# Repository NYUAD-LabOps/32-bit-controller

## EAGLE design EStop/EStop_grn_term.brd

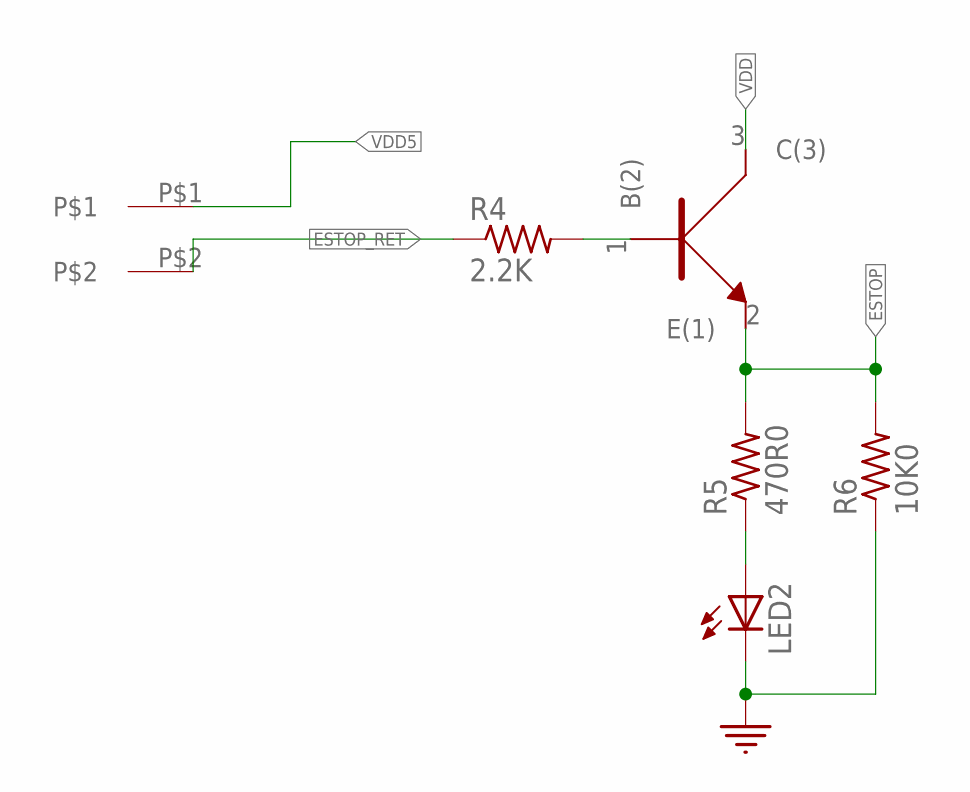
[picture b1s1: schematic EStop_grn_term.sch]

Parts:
J1: 2-pos; 2_3.81MM_PITCH
LED2: Green; 0805
R4: 2.2K; 0402
R5: 470R0; 0402
R6: 10K0; 0402
U2: NPN; SOT323

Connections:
ESTOP: R5.P$2 (2), R6.P$2 (2), U2.2 (E(1))
ESTOP_RET: J1.P$2, R4.P$1 (1)
GND: LED2.2 (C), R6.P$1 (1)
unnamed: R4.P$2 (2), U2.1 (B(2))
unnamed: LED2.1 (A), R5.P$1 (1)
VDD: U2.3 (C(3))
VDD5: J1.P$1

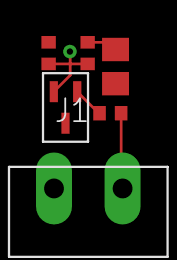
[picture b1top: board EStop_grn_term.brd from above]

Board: 2 copper layers, 6 parts (0 on the bottom side), 5 nets.

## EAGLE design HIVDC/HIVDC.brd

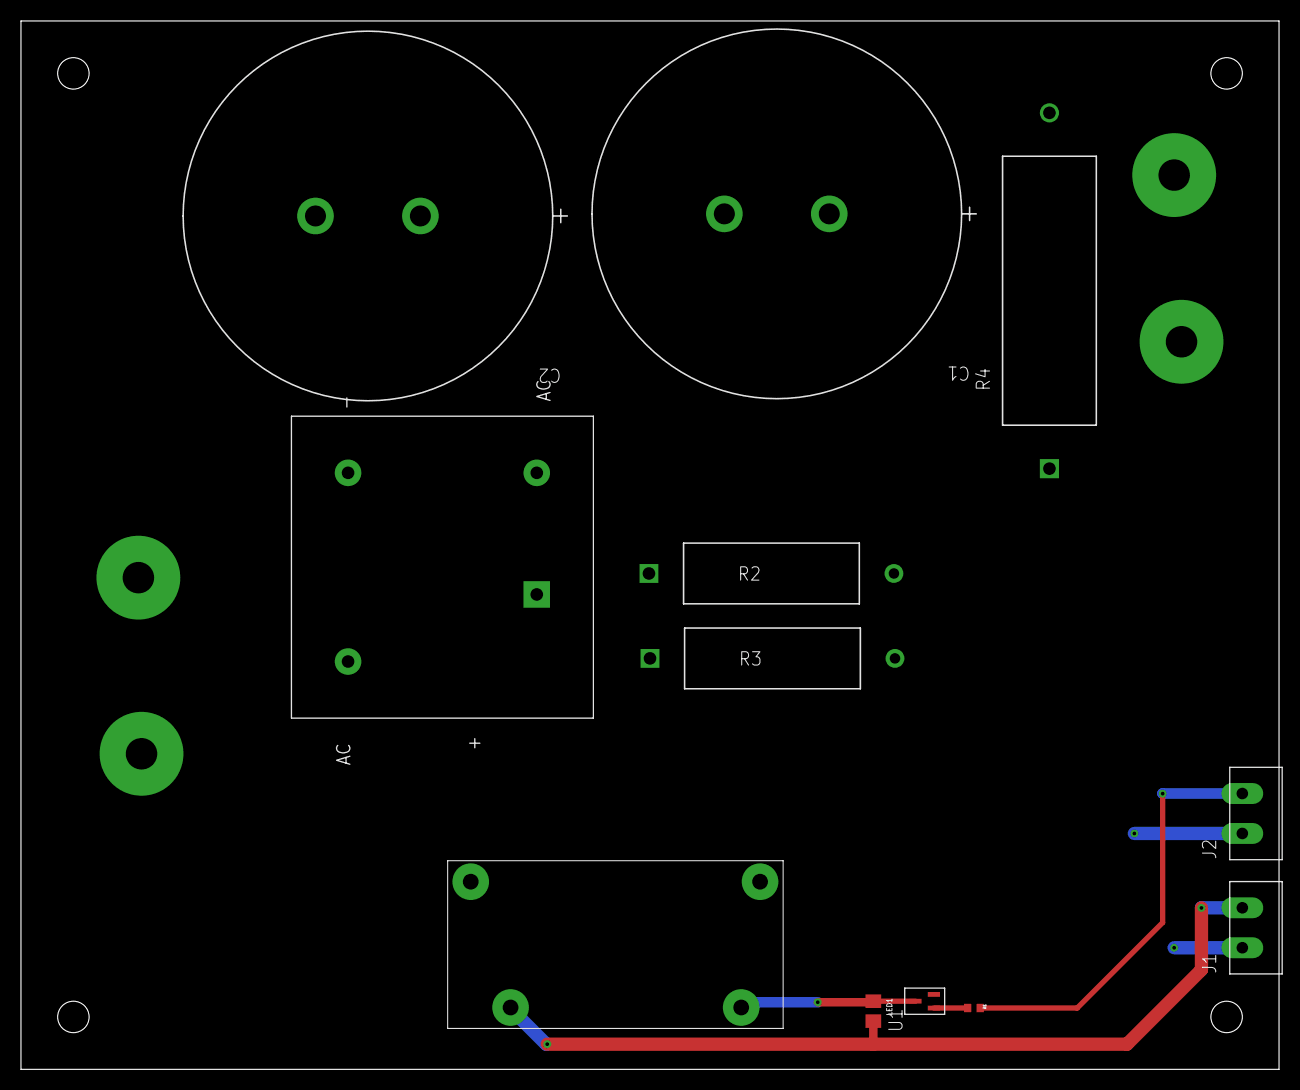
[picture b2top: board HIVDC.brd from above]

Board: 2 copper layers, 120.0 x 100.0 mm, 16 parts (0 on the bottom side), 11 nets.

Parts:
AC_L1: AC_240V_L1_15A
AC_N: AC_240V_L1_15A
C1, C2: SLP152M250H9P3; CAP_SLP152M250H9P3_CND
J1, J2: 2-pos; 2_3.81MM_PITCH
L1, L2: AC_240V_L1_15A
LED1: Green; 0805
R1: 0402
R2, R3: RSF200JB-73-22R; YAG_RSF200_YAG
R4: RS00547K00FE73; RS005_VIS
RL1: J120D
U1: NPN; SOT323
U$1: KBPC5010W-G; KBPC-W_THRU

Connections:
AC_L1: AC_L1.P$1, U$1.1
AC_N: AC_N.P$1, U$1.3
CAP_TO_CAP_1: C1.2, C2.1
DC+: C1.1, L1.P$1, R2.2, R3.2, R4.2, RL1.P$3
DC+_OUT: R2.1, R3.1, RL1.P$4, U$1.4
DC-: C2.2, L2.P$1, R4.1, U$1.2
GND: J1.P$1, J2.P$1, U1.2
unnamed: LED1.1, RL1.P$2, U1.3
VDD5: J2.P$2, R1.P$1
VDD12: J1.P$2, LED1.2, RL1.P$1
V_G: R1.P$2, U1.1

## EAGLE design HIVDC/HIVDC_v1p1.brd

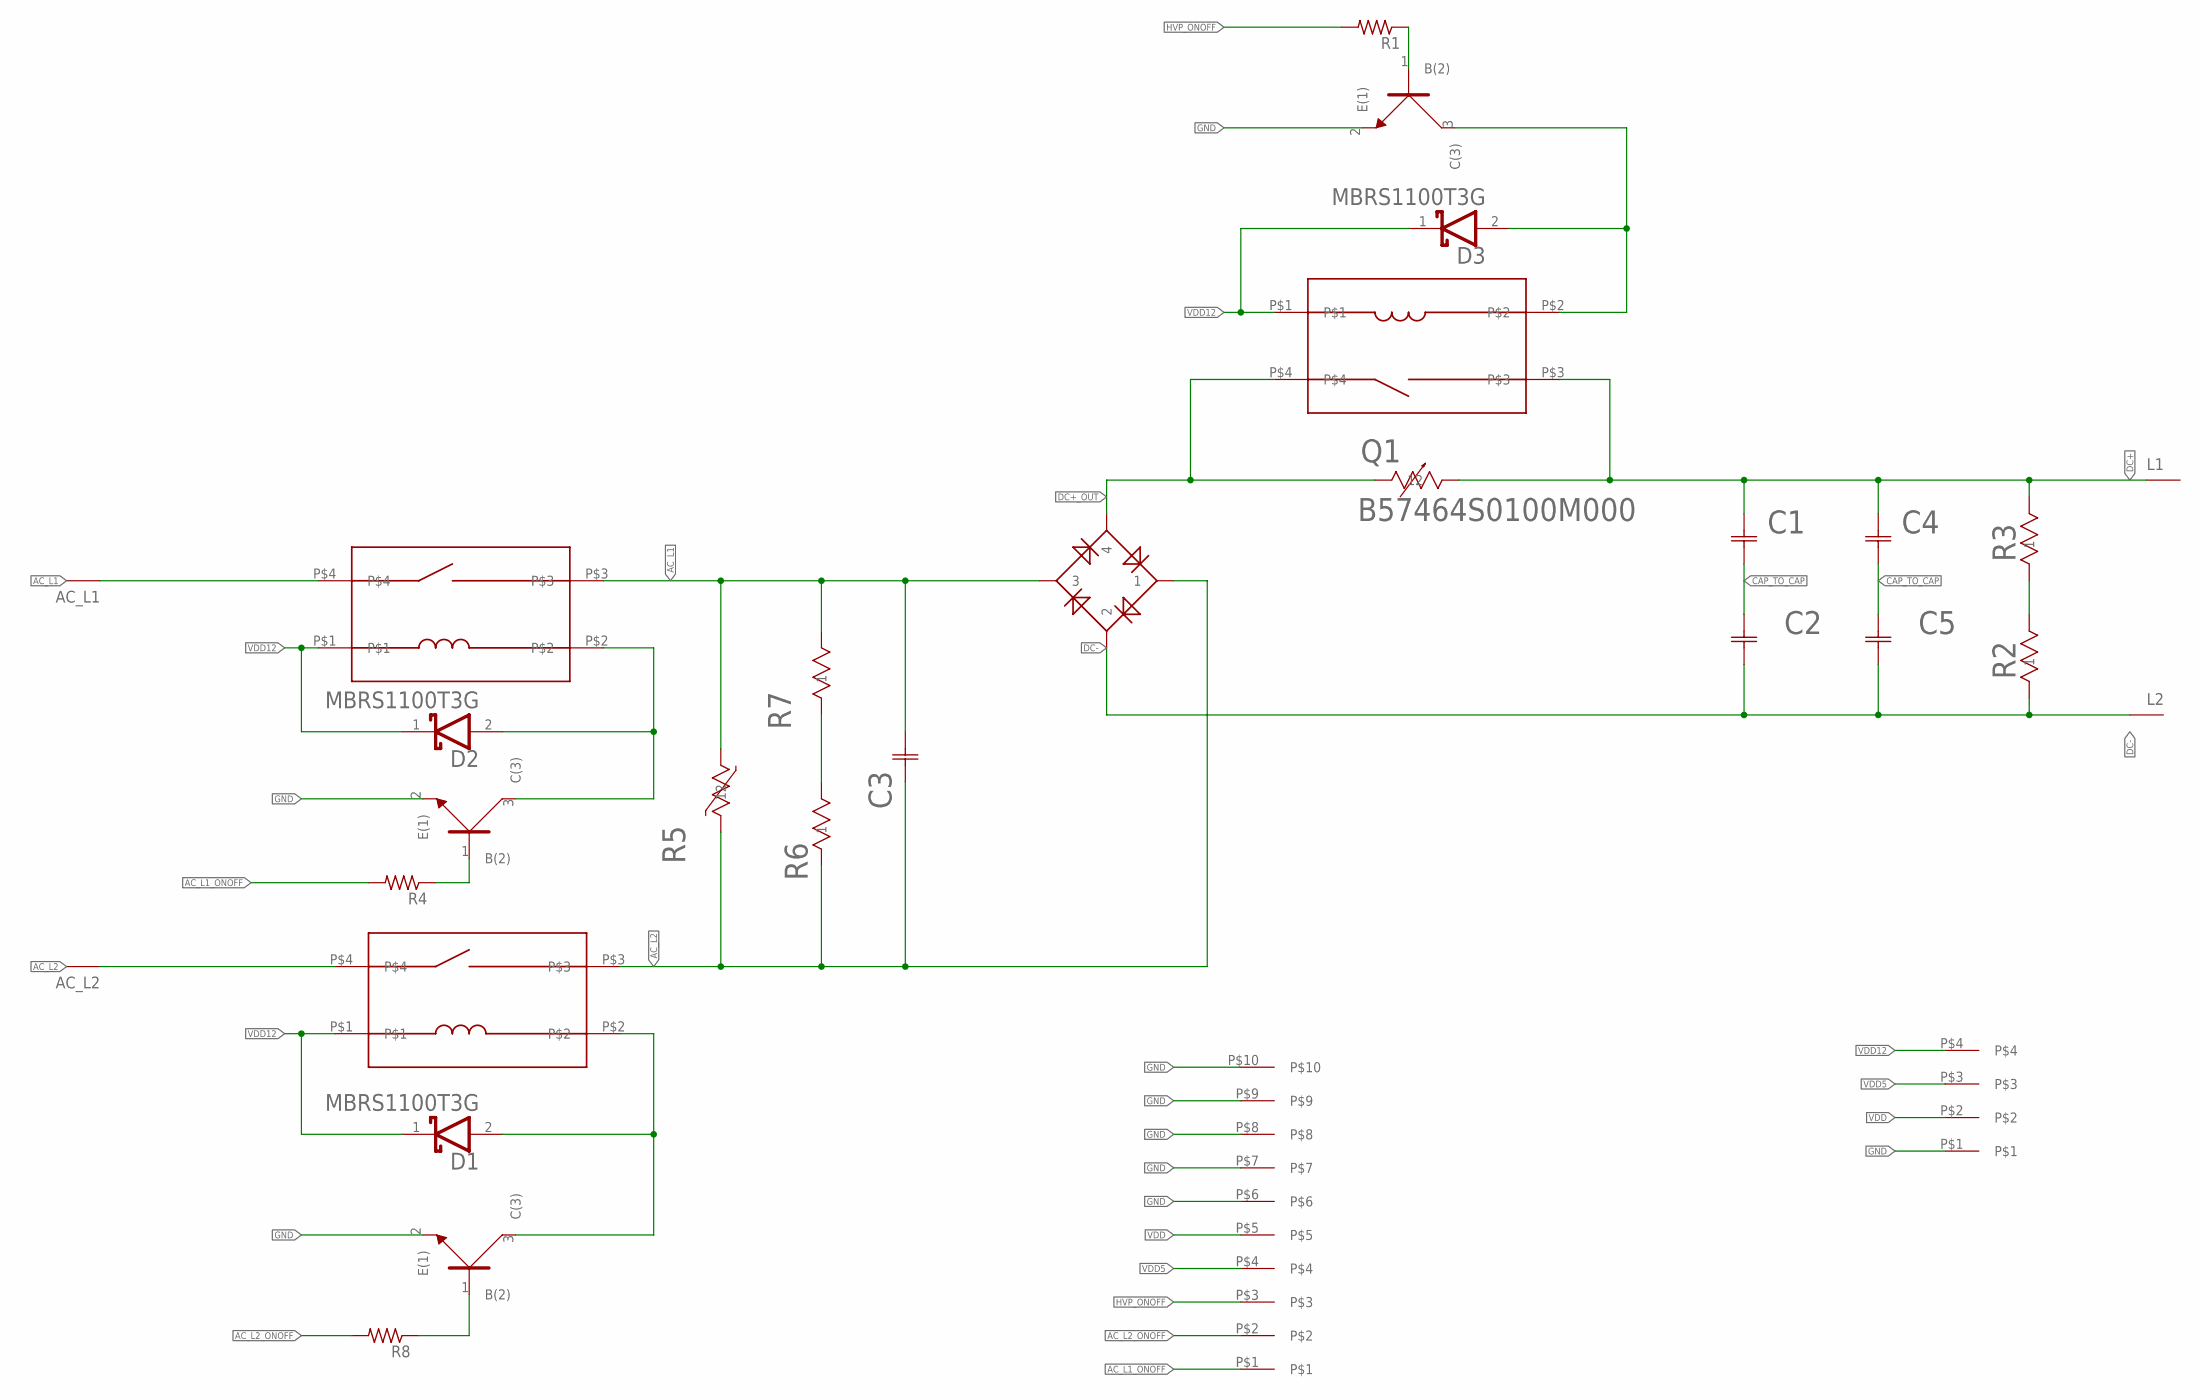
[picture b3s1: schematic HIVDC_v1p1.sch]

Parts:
AC_L1: AC_240V_N_15A; AC_240V_L1_15A
AC_L2: AC_240V_L_15A; AC_240V_L1_15A
C1, C2, C4, C5: SLP152M250H9P3; CAP_SLP152M250H9P3_CND
C3: B32922C3104K; CAP_5.0_X_10.5_X_18.0_EPC
D1, D2, D3: MBRS1100T3GON_SEMI_MBRS1100T3G_0_0; SMB
J1: 4-pos; 1X4_3.81MM_PITCH
L1, L2: DC_HI_V; AC_240V_L1_15A
Q1: B57464S0100M000; TRES_B57464S0XXXM000_EPC
R1, R4, R8: R_0402; 0402
R2, R3, R6, R7: CRCW1206220KJNEAHPRES_V1206_VIS-M; RES_V1206_VIS-M
R5: VDRUS10T510BSE; VRES_VDRUS10T460BSE_VIS
RL1, RL2, RL3: J120D1AS12VDCP; J120D
U1, U2, U3: NPN; SOT323
U$1: KBPC5010W-G; KBPC-W_THRU
U$3: 1_X_10_HEADER_GENERIC_.1INCH; HEADER_1_X_10_.1_INCH

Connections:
AC_L1: AC_L1.P$1, C3.2, R5.1 (11), R7.2, RL2.P$3, RL2.P$4, U$1.3
AC_L1_ONOFF: R4.P$2 (2), U$3.P$1
AC_L2: AC_L2.P$1, C3.1, R5.2 (12), R6.1, RL3.P$3, RL3.P$4, U$1.1
AC_L2_ONOFF: R8.P$2 (2), U$3.P$2
CAP_TO_CAP: C1.2, C2.1, C4.2, C5.1
DC+: C1.1, C4.1, L1.P$1, Q1.1 (11), R3.2, RL1.P$3
DC+_OUT: Q1.2 (12), RL1.P$4, U$1.4
DC-: C2.2, C5.2, L2.P$1, R2.1, U$1.2
GND: J1.P$1, U1.2 (E(1)), U2.2 (E(1)), U3.2 (E(1)), U$3.P$6, U$3.P$7, U$3.P$8, U$3.P$9, U$3.P$10
HVP_ONOFF: R1.P$2 (2), U$3.P$3
unnamed: D3.2 (ANODE), RL1.P$2, U1.3 (C(3))
unnamed: R6.2, R7.1
unnamed: R2.2, R3.1
unnamed: R1.P$1 (1), U1.1 (B(2))
unnamed: D2.2 (ANODE), RL2.P$2, U2.3 (C(3))
unnamed: R4.P$1 (1), U2.1 (B(2))
unnamed: D1.2 (ANODE), RL3.P$2, U3.3 (C(3))
unnamed: R8.P$1 (1), U3.1 (B(2))
VDD: J1.P$2, U$3.P$5
VDD5: J1.P$3, U$3.P$4
VDD12: D1.1 (CATHODE), D2.1 (CATHODE), D3.1 (CATHODE), J1.P$4, RL1.P$1, RL2.P$1, RL3.P$1

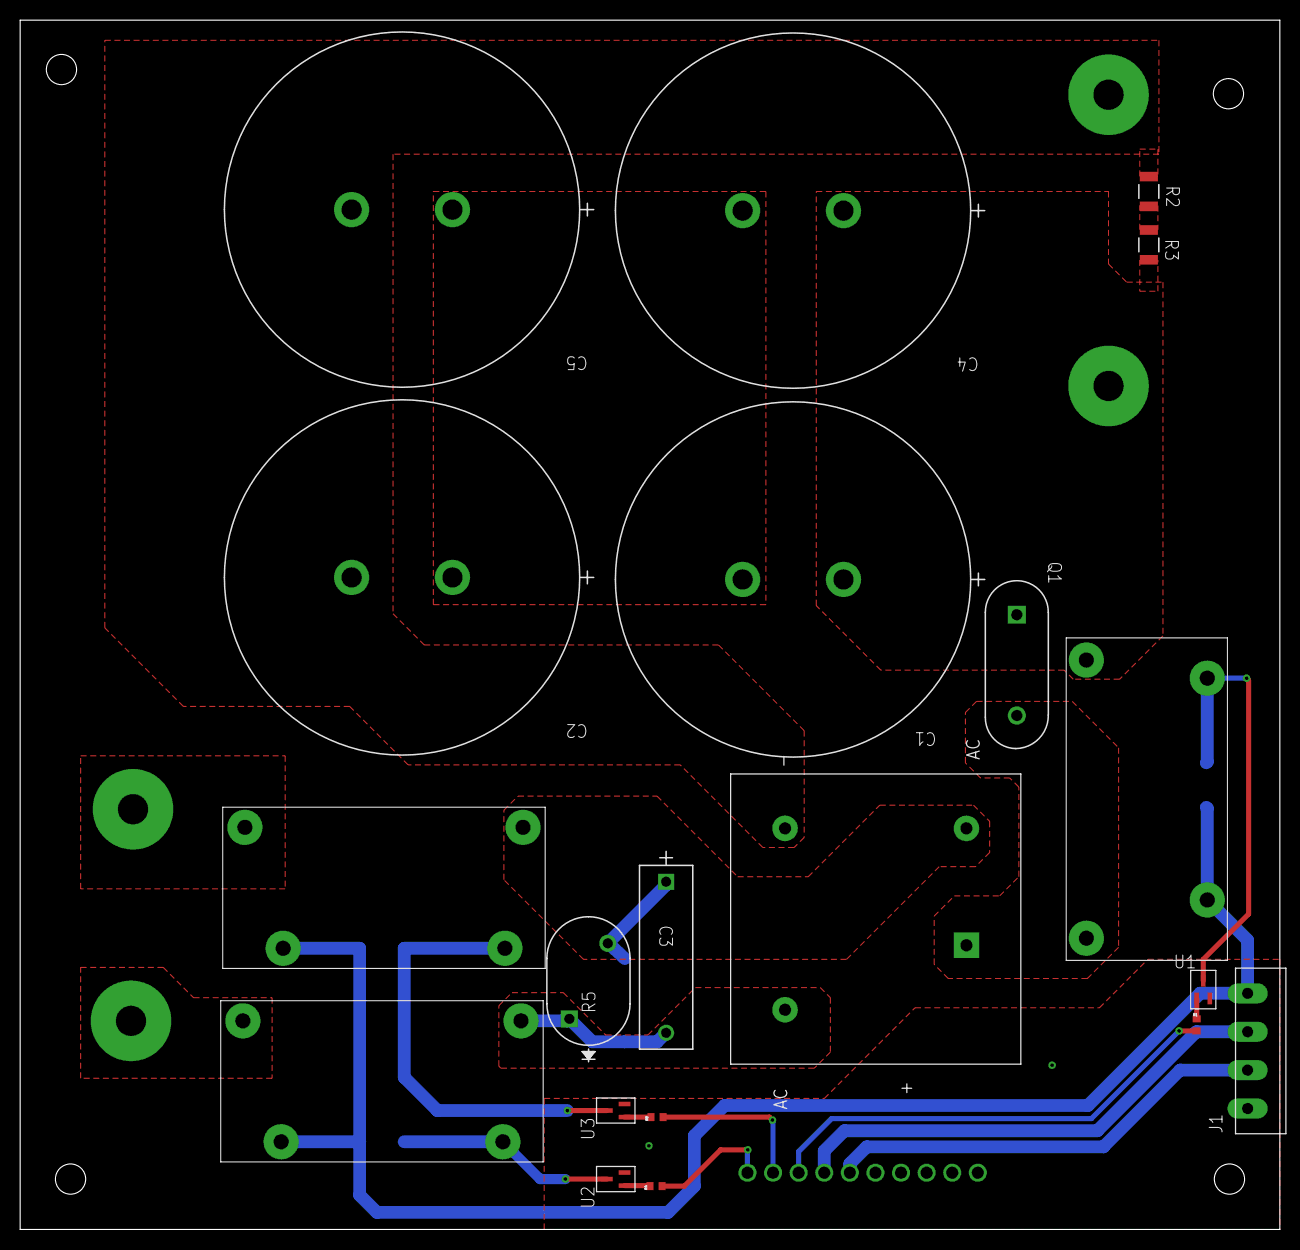
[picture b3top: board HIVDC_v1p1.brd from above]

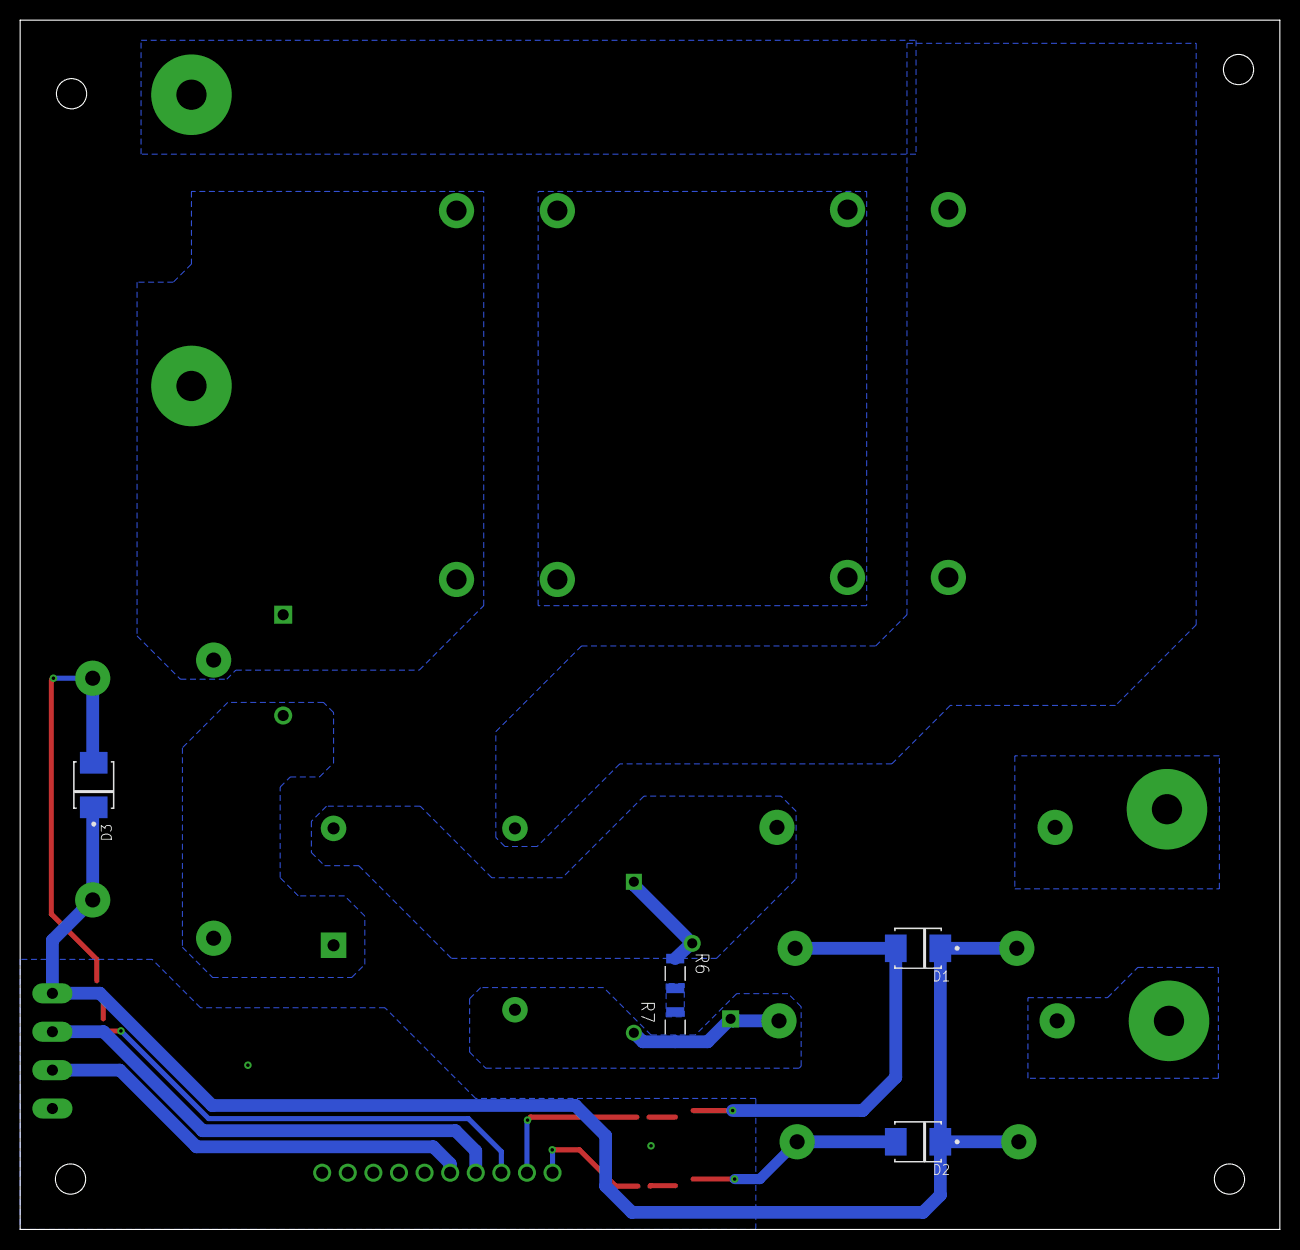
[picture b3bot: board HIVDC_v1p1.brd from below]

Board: 2 copper layers, 125.0 x 120.0 mm, 30 parts (5 on the bottom side), 21 nets.

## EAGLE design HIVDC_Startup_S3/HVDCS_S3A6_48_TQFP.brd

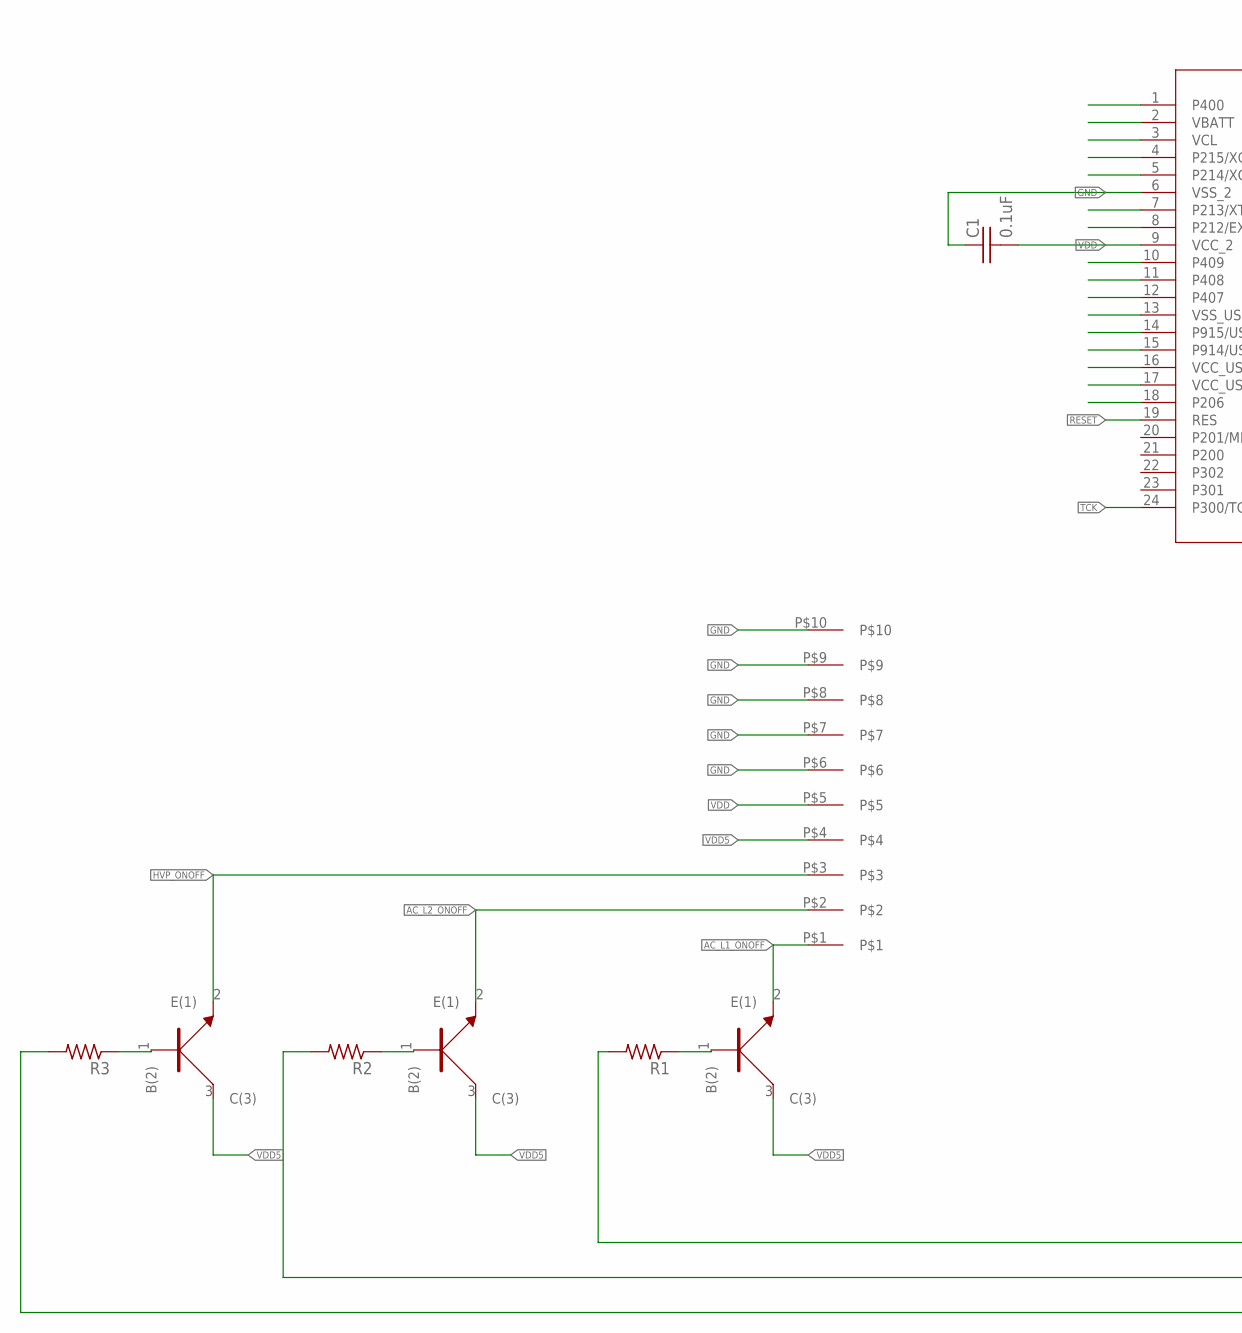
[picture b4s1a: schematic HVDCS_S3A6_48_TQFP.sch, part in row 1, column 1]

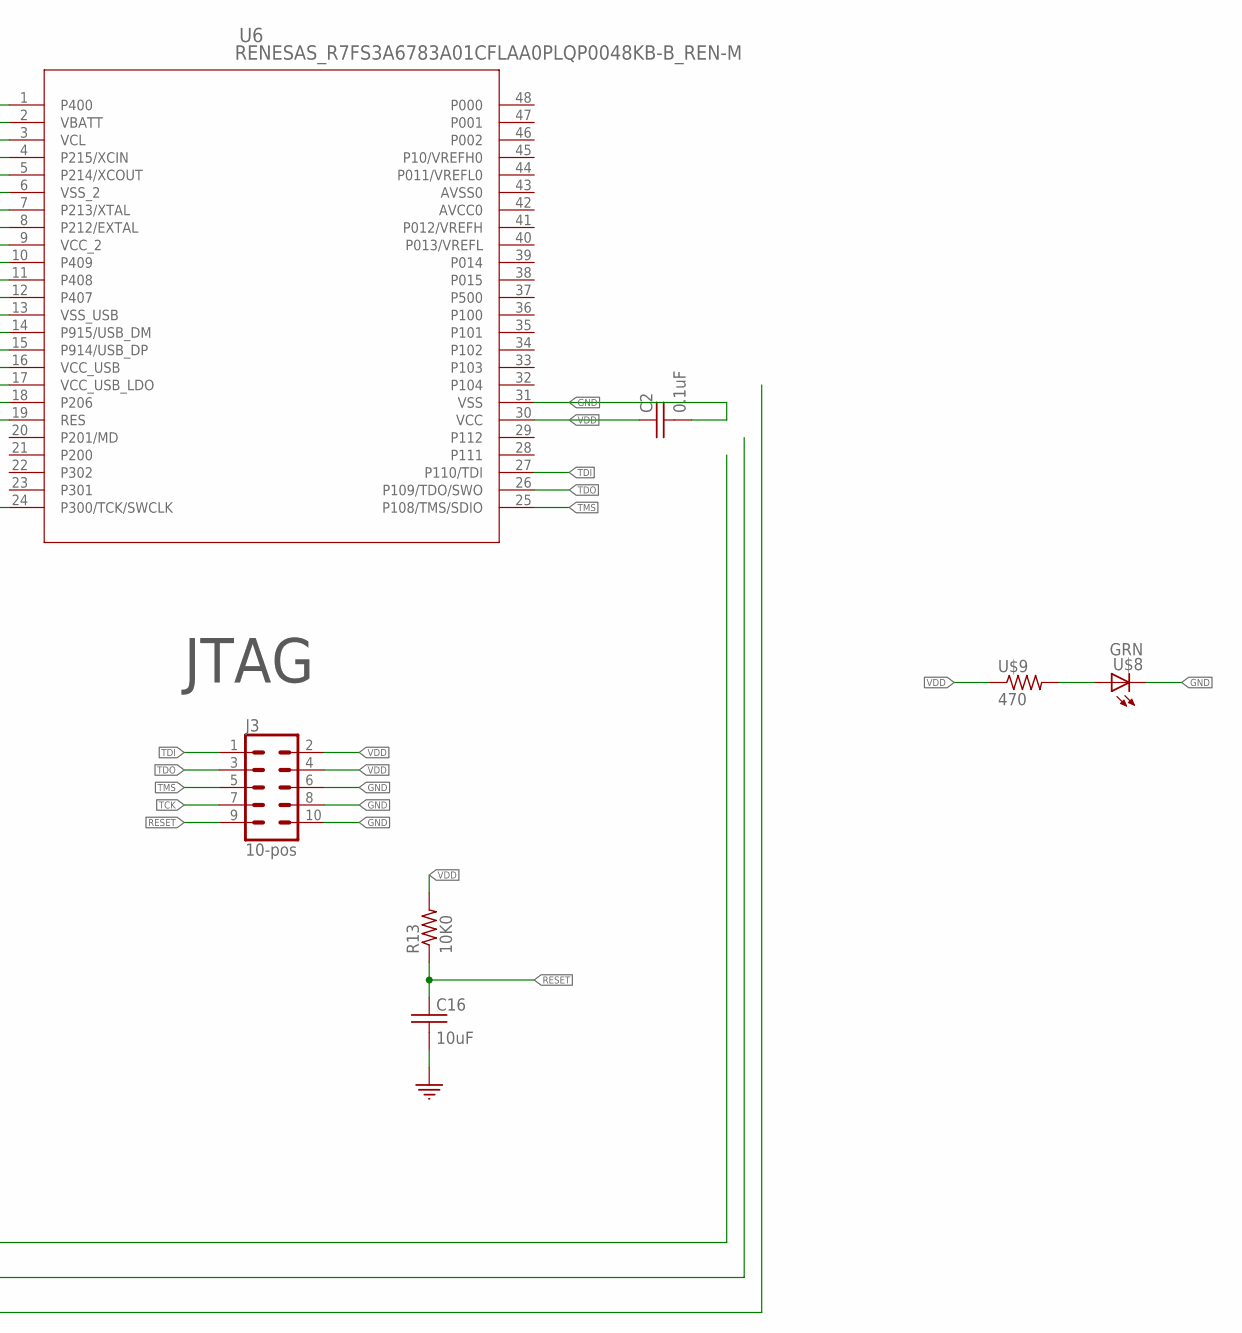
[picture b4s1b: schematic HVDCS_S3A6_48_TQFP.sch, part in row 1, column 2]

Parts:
C1, C2: 0.1uF; 0402
C16: 10uF; 0402
J3: 10-pos; 2X5
R1, R2, R3: R_0402; 0402
R13: 10K0; 0402
U1, U2, U3: NPN; SOT323
U6: RENESAS_R7FS3A6783A01CFLAA0PLQP0048KB-B_REN-M; PLQP0048KB-B_REN-M
U$5: 1_X_10_HEADER_GENERIC_.1INCH; HEADER_1_X_10_.1_INCH
U$8: LED_0805_GREEN
U$9: R_0805_470

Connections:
AC_L1_ONOFF: U1.2 (E(1)), U$5.P$1
AC_L2_ONOFF: U2.2 (E(1)), U$5.P$2
AVCC0: U6.42 (AVCC0)
GND: C1.P$1 (1), C2.P$2 (2), C16.P$2 (2), J3.6, J3.8, J3.10, U6.6 (VSS_2), U6.31 (VSS), U$5.P$6, U$5.P$7, U$5.P$8, U$5.P$9, U$5.P$10, U$8.C
HVP_ONOFF: U3.2 (E(1)), U$5.P$3
unnamed: U$8.A, U$9.2
unnamed: R1.P$1 (1), U1.1 (B(2))
unnamed: R2.P$1 (1), U2.1 (B(2))
unnamed: R3.P$1 (1), U3.1 (B(2))
P1.5: R3.P$2 (2)
P1.6: R2.P$2 (2)
P1.7: R1.P$2 (2)
P10/VREFH0: U6.45 (P10/VREFH0)
P011/VREFL0: U6.44 (P011/VREFL0)
P012/VREFH: U6.41 (P012/VREFH)
P013/VREFL: U6.40 (P013/VREFL)
RESET: C16.P$1 (1), J3.9, R13.P$1 (1), U6.19 (RES)
TCK: J3.7, U6.24 (P300/TCK/SWCLK)
TDI: J3.1, U6.27 (P110/TDI)
TDO: J3.3, U6.26 (P109/TDO/SWO)
TMS: J3.5, U6.25 (P108/TMS/SDIO)
VDD: C1.P$2 (2), C2.P$1 (1), J3.2, J3.4, R13.P$2 (2), U6.9 (VCC_2), U6.30 (VCC), U$5.P$5, U$9.1
VDD5: U1.3 (C(3)), U2.3 (C(3)), U3.3 (C(3)), U$5.P$4

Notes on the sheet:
JTAG

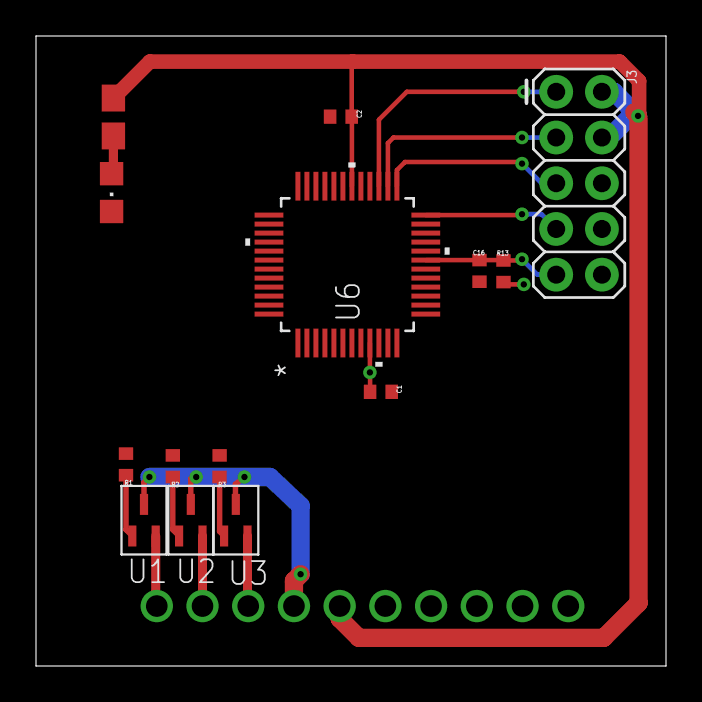
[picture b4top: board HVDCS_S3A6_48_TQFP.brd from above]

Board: 2 copper layers, 35.0 x 35.0 mm, 15 parts (0 on the bottom side), 15 nets.

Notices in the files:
parts and their libraries:
COPYRIGHT: Copyright (C) 2018 Accelerated Designs. All rights reserved
COPYRIGHT: Copyright (C) 2021 Accelerated Designs. All rights reserved
